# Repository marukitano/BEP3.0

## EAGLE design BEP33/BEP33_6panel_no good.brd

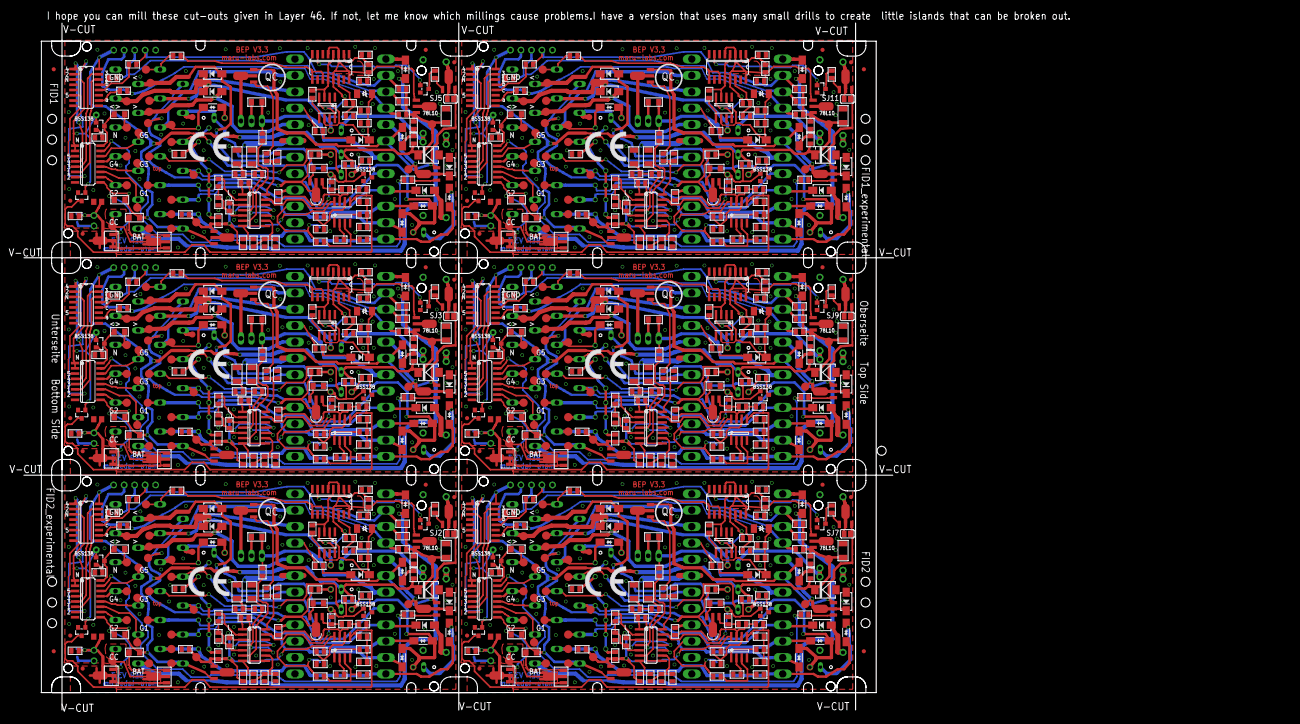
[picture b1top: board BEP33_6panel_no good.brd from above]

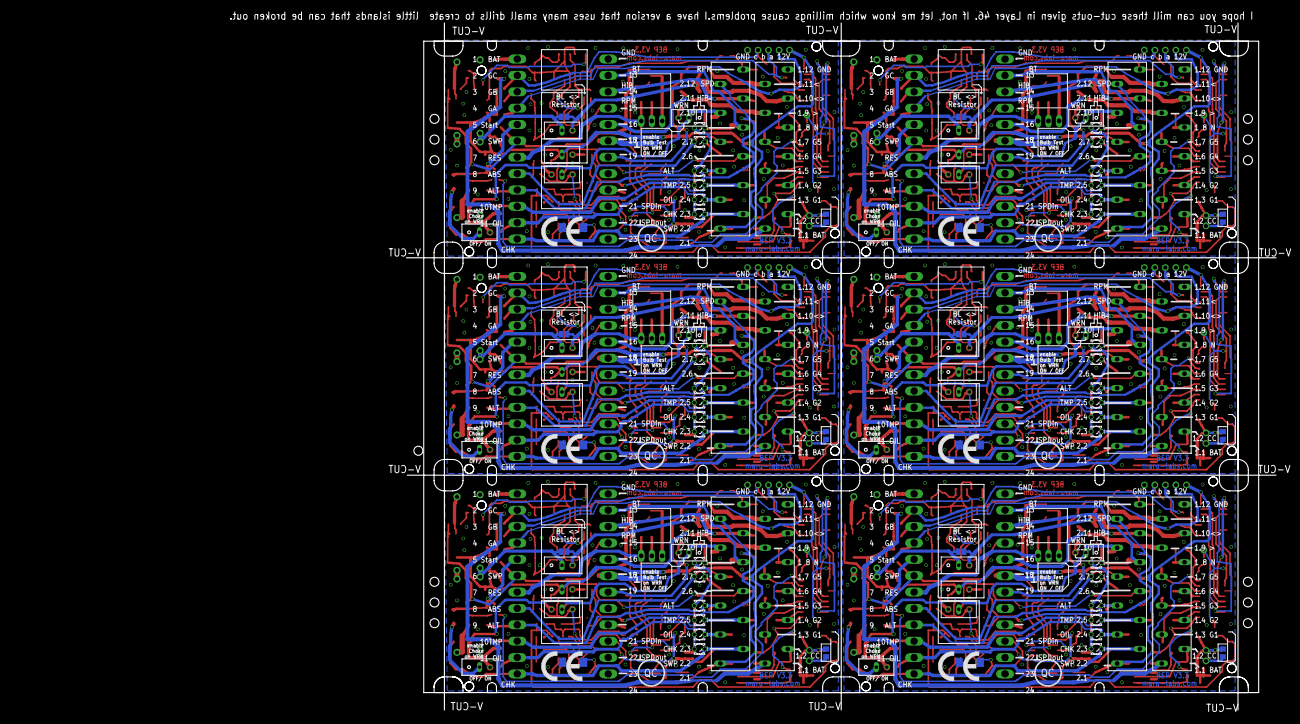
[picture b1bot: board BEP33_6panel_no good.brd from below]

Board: 2 copper layers, 210.4 x 166.2 mm, 904 parts (150 on the bottom side), 533 nets.

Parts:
1, 2, 3, 4, 5, 6, 7, 8, 9, 10, 11, 12: 12-PIN
6V, 6V1, 6V2, 6V3, 6V4, 6V5, 10V, 10V1, 10V2, 10V3, 10V4, 10V5: TPSB2.0; B2.0
C1, C3, C14, C16, C27, C28, C39, C40, C51, C52, C107, C108: 100u; C1206
C2, C13, C26, C38, C50, C62: 10u; C1206
C4, C11, C17, C24, C29, C36, C41, C48, C53, C60, C103, C104: 100nF,; C0805
C5, C12, C15, C18, C25, C30, C37, C42, C49, C54, C61, C101: 4.7u; C0805
C6, C7, C19, C20, C31, C32, C43, C44, C55, C56, C105, C106: 100nF.; C0805
C8, C21, C33, C45, C57, C109: 2.2nF; C0805
C9, C10, C22, C23, C34, C35, C46, C47, C58, C59, C102, C110: 100nF; C0805
D1, D2, D15, D16, D29, D30, D43, D44, D57, D58, D71, D72: SS12; DO-214AC_SLIM
D3, D5, D18, D19, D32, D33, D46, D47, D60, D61, D102, D103: 1N4007,; DO-214AC
D4, D17, D31, D45, D59, D73: Zen11; SOD-123_MINI-SMA
D6, D11, D20, D25, D34, D39, D48, D53, D62, D67, D105, D106: 1N4007.; DO-214AC
D7, D10, D21, D24, D35, D38, D49, D52, D63, D66, D107, D110: 1N5817; DO-214AC_SLIM
D8, D9, D22, D23, D36, D37, D50, D51, D64, D65, D108, D109: 1N5817.; DO-214AC_SLIM
D12, D26, D40, D54, D68, D112: 1N4007; DO-214AC
D13, D27, D41, D55, D69, D101: Zen15; DO214AA
D14, D28, D42, D56, D70, D104: SM6TDO214AA_BI; DO214AA_BI
FID1, FID2, FID3, FID4, FID5, FID6, FID7, FID8, FID9, FID10, FID11, FID12, FID13, FID14, FID15, FID16, FID17, FID18, FID19, FID20, FID21, FID22, FID101, FID102, FID103, FID104: FIDUCIAL; FIDUCIAL_1MM
FID1B, FID2B: FIDUCIALFIDUCIAL_1MM_WITH_SOLDERMASK; FIDUCIAL_1MM_WITH_SOLDERMASK
IC1, IC10, IC19, IC28, IC37, IC105: 4028; SO16
IC2, IC11, IC20, IC29, IC38, IC109: 317TO202H_NOHOLE; TO220H_NOHOLE
IC3, IC12, IC21, IC30, IC39, IC107: ULN2004; SO16
IC4, IC13, IC22, IC31, IC40, IC108: LM339; SO14
IC5, IC14, IC23, IC32, IC41, IC102: 78L06; SOT89_ROUND
IC6, IC15, IC24, IC33, IC42, IC110: 555; SO08
IC7, IC16, IC25, IC34, IC43, IC111: 4538; SO16
IC8, IC17, IC26, IC35, IC44, IC104: 78L10; SOT89_ROUND
IC9, IC18, IC27, IC36, IC45, IC101: LM2904; SO08
JP1, JP3, JP4, JP5, JP6, JP8, JP9, JP10, JP11, JP13, JP14, JP15, JP16, JP18, JP19, JP20, JP21, JP23, JP24, JP25, JP101, JP102, JP103, JP104: JP2_SMALLPADS
JP2, JP7, JP12, JP17, JP22, JP105: JP2E_ORIG; JP2_ORIG_SMALLPADS
LED1, LED2, LED3, LED4, LED5, LED6, LED7, LED8, LED9, LED10, LED11, LED12, LED13, LED14, LED15, LED16, LED17, LED18, LED19, LED20, LED21, LED22, LED23, LED24, LED25, LED26, LED27, LED28, LED29, LED30, LED101, LED102, LED103, LED104, LED105, LED106: LD260
Q1, Q3, Q9, Q10, Q11, Q13, Q19, Q20, Q21, Q23, Q29, Q30, Q31, Q33, Q39, Q40, Q41, Q43, Q49, Q50, Q51, Q53, Q106, Q107: J1; SOT-23
Q2, Q4, Q7, Q12, Q14, Q17, Q22, Q24, Q27, Q32, Q34, Q37, Q42, Q44, Q47, Q52, Q104, Q105: BA; SOT89
Q5, Q6, Q15, Q16, Q25, Q26, Q35, Q36, Q45, Q46, Q101, Q102: BA.; SOT89
Q8, Q18, Q28, Q38, Q48, Q103: MY; SOT89
R1, R2, R3, R10, R15, R16, R17, R22, R23, R41, R42, R56, R57, R58, R64, R70, R71, R72, R77, R78, R96, R97, R109, R110, R111, R125, R130, R135, R141, R155, R156, R157, R163, R169, R170, R171, R176, R177, R195, R196, R210, R211, R212, R218, R224, R225, R226, R231, R232, R250, R251, R265, R266, R267, R273, R279, R280, R281, R286, R287, R305, R306, R320, R321, R322, R328: 104; R0805
R4, R12, R13, R40, R61, R65, R66, R95, R138, R160, R164, R165, R194, R215, R219, R220, R249, R270, R274, R275, R304, R325, R329, R330: 100; R0805
R5, R9, R11, R36, R37, R59, R62, R68, R91, R92, R102, R106, R134, R158, R161, R167, R190, R191, R213, R216, R222, R245, R246, R268, R271, R277, R300, R301, R323, R326: 13; R1206
R6, R26, R48, R60, R81, R119, R133, R147, R159, R180, R202, R214, R235, R257, R269, R290, R312, R324: 2201; R0805
R7, R14, R45, R46, R67, R69, R100, R118, R127, R129, R136, R137, R166, R168, R199, R200, R221, R223, R254, R255, R276, R278, R309, R310: 47; V235/17_1MM
R8, R18, R28, R39, R63, R73, R83, R94, R105, R116, R126, R162, R172, R182, R193, R217, R227, R237, R248, R272, R282, R292, R303, R327: 4701; R0805
R19, R20, R25, R27, R49, R50, R53, R54, R74, R75, R80, R82, R107, R108, R113, R114, R120, R124, R132, R146, R148, R149, R152, R153, R173, R174, R179, R181, R203, R204, R207, R208, R228, R229, R234, R236, R258, R259, R262, R263, R283, R284, R289, R291, R313, R314, R317, R318: 1002; R0805
R21, R24, R76, R79, R121, R131, R175, R178, R230, R233, R285, R288: 1502; R0805
R29, R38, R44, R47, R52, R84, R93, R99, R117, R122, R123, R139, R140, R145, R151, R183, R192, R198, R201, R206, R238, R247, R253, R256, R261, R293, R302, R308, R311, R316: 2702; R0805
R30, R32, R35, R51, R85, R87, R90, R101, R112, R115, R128, R150, R184, R186, R189, R205, R239, R241, R244, R260, R294, R296, R299, R315: 102; R0805
R31, R55, R86, R103, R104, R154, R185, R209, R240, R264, R295, R319: R_user; R0805
R33, R88, R143, R187, R242, R297: (101); R0805
R34, R89, R142, R188, R243, R298: (1000); R0805
R43, R98, R144, R197, R252, R307: (1002); R0805
SJ1, SJ2, SJ3, SJ4, SJ5, SJ6, SJ7, SJ8, SJ9, SJ10, SJ11, SJ101: SJ
START, START1, START2, START3, START4, START5: TPSB2.0; B2.0
TP1, TP2, TP3, TP4, TP5, TP6, TP7, TP8, TP9, TP10, TP11, TP12, TP13, TP14, TP15, TP16, TP17, TP18, TP19, TP20, TP21, TP22, TP23, TP25, TP26, TP27, TP28, TP29, TP30, TP31, TP32, TP33, TP34, TP35, TP36, TP37, TP38, TP39, TP40, TP41, TP43, TP44, TP45, TP46, TP47, TP48, TP49, TP50, TP51, TP52, TP53, TP54, TP55, TP56, TP57, TP58, TP59, TP60, TP61, TP62, TP63, TP64, TP66, TP67, TP68, TP69, TP70, TP71, TP72, TP73, TP74, TP75, TP76, TP77, TP78, TP79, TP80, TP81, TP82, TP83, TP84, TP85, TP86, TP87, TP89, TP90, TP91, TP92, TP93, TP94, TP95, TP96, TP97, TP98, TP99, TP100, TP101, TP102, TP103, TP104, TP105, TP106, TP107, TP108, TP109, TP110, TP112, TP113, TP114, TP115, TP116, TP117, TP118, TP119, TP120, TP121, TP122, TP123, TP124, TP125, TP126, TP127, TP128, TP129, TP130, TP131, TP132, TP133, TP135, TP136, TP137, TP138: TPSB2.0; B2.0
TP24, TP42, TP65, TP88, TP111, TP134: TPSB1,27; B1,27
U$1, U$2, U$3, U$4, U$5, U$6, U$7, U$8, U$9, U$10, U$11, U$12: CE_10.00
X1, X4, X7, X10, X13, X101: 24-PIN_V2
X2, X5, X8, X11, X14, X103: 22-23-2051
X3, X6, X9, X12, X15, X102: 22-23-2021

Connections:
+10V: 10V.TP, 10V1.TP, 10V2.TP, 10V3.TP, 10V4.TP, 10V5.TP, C9.1, C22.1, C34.1, C46.1, C58.1, C102.1, IC6.4, IC6.8, IC7.3, IC7.5, IC7.13, IC7.16, IC8.1, IC15.4, IC15.8, IC16.3, IC16.5, IC16.13, IC16.16, IC17.1, IC24.4, IC24.8, IC25.3, IC25.5, IC25.13, IC25.16, IC26.1, IC33.4, IC33.8, IC34.3, IC34.5, IC34.13, IC34.16, IC35.1, IC42.4, IC42.8, IC43.3, IC43.5, IC43.13, IC43.16, IC44.1, IC104.1, IC110.4, IC110.8, IC111.3, IC111.5, IC111.13, IC111.16, R10.2, R47.2, R64.2, R139.2, R145.2, R163.2, R201.2, R218.2, R256.2, R273.2, R311.2, R328.2
+12V: 2.1, 4.1, 6.1, 8.1, 10.1, 12.1, C2.1, C13.1, C26.1, C38.1, C50.1, C62.1, D13.C, D27.C, D41.C, D55.C, D69.C, D101.C, IC1.16, IC3.9, IC5.3, IC8.3, IC10.16, IC12.9, IC14.3, IC17.3, IC19.16, IC21.9, IC23.3, IC26.3, IC28.16, IC30.9, IC32.3, IC35.3, IC37.16, IC39.9, IC41.3, IC44.3, IC102.3, IC104.3, IC105.16, IC107.9, JP1.2, JP6.2, JP11.2, JP16.2, JP21.2, JP101.2, R12.2, R13.2, R15.2, R16.2, R17.2, R36.1, R37.1, R41.1, R65.2, R66.2, R70.2, R71.2, R72.2, R91.1, R92.1, R96.1, R102.1, R106.1, R109.2, R110.2, R111.2, R135.1, R164.2, R165.2, R169.2, R170.2, R171.2, R190.1, R191.1, R195.1, R219.2, R220.2, R224.2, R225.2, R226.2, R245.1, R246.1, R250.1, R274.2, R275.2, R279.2, R280.2, R281.2, R300.1, R301.1, R305.1, R329.2, R330.2, TP12.TP, TP45.TP, TP68.TP, TP91.TP, TP114.TP, TP137.TP, X2.1, X5.1, X8.1, X11.1, X14.1, X103.1
+12V1: 2.11, Q103.2, R119.1, TP26.TP
+12V2: 4.11, Q8.2, R48.1, TP44.TP
+12V3: 6.11, Q18.2, R147.1, TP67.TP
+12V4: 8.11, Q28.2, R202.1, TP90.TP
+12V5: 10.11, Q38.2, R257.1, TP113.TP
+12V6: 12.11, Q48.2, R312.1, TP136.TP
GND: 1.12, 3.12, 5.12, 7.12, 9.12, 11.12, C1.2, C2.2, C3.2, C4.2, C5.2, C6.2, C7.1, C8.1, C9.2, C10.2, C11.2, C12.1, C13.2, C14.2, C15.1, C16.2, C17.2, C18.2, C19.2, C20.1, C21.1, C22.2, C23.2, C24.2, C25.1, C26.2, C27.2, C28.2, C29.2, C30.2, C31.2, C32.1, C33.1, C34.2, C35.2, C36.2, C37.1, C38.2, C39.2, C40.2, C41.2, C42.2, C43.2, C44.1, C45.1, C46.2, C47.2, C48.2, C49.1, C50.2, C51.2, C52.2, C53.2, C54.2, C55.2, C56.1, C57.1, C58.2, C59.2, C60.2, C61.1, C62.2, C101.2, C102.2, C103.2, C104.2, C105.2, C106.1, C107.2, C108.2, C109.1, C110.2, D4.A, D11.1, D13.A, D14.A, D17.A, D25.1, D27.A, D28.A, D31.A, D39.1, D41.A, D42.A, D45.A, D53.1, D55.A, D56.A, D59.A, D67.1, D69.A, D70.A, D73.A, D101.A, D104.A, D105.1, IC1.8, IC1.11, IC3.8, IC4.12, IC5.2, IC5.2@1, IC6.1, IC7.1, IC7.8, IC7.15, IC8.2, IC8.2@1, IC9.4, IC10.8, IC10.11, IC12.8, IC13.12, IC14.2, IC14.2@1, IC15.1, IC16.1, IC16.8, IC16.15, IC17.2, IC17.2@1, IC18.4, IC19.8, IC19.11, IC21.8, IC22.12, IC23.2, IC23.2@1, IC24.1, IC25.1, IC25.8, IC25.15, IC26.2, IC26.2@1, IC27.4, IC28.8, IC28.11, IC30.8, IC31.12, IC32.2, IC32.2@1, IC33.1, IC34.1, IC34.8, IC34.15, IC35.2, IC35.2@1, IC36.4, IC37.8, IC37.11, IC39.8, IC40.12, IC41.2, IC41.2@1, IC42.1, IC43.1, IC43.8, IC43.15, IC44.2, IC44.2@1, IC45.4, IC101.4, IC102.2, IC102.2@1, IC104.2, IC104.2@1, IC105.8, IC105.11, IC107.8, IC108.12, IC110.1, IC111.1, IC111.8, IC111.15, Q1.2, Q3.2, Q9.2, Q11.2, Q13.2, Q19.2, Q21.2, Q23.2, Q29.2, Q31.2, Q33.2, Q39.2, Q41.2, Q43.2, Q49.2, Q51.2, Q53.2, Q107.2, R4.1, R5.2, R6.2, R19.1, R25.1, R29.1, R30.2, R31.2, R33.2, R42.2, R45.1, R46.1, R54.1, R55.2, R59.2, R60.2, R61.1, R74.1, R80.1, R84.1, R85.2, R86.2, R88.2, R97.2, R100.1, R101.2, R103.2, R104.2, R107.1, R114.1, R118.1, R123.1, R132.1, R136.1, R137.1, R141.2, R143.2, R153.1, R154.2, R158.2, R159.2, R160.1, R173.1, R179.1, R183.1, R184.2, R185.2, R187.2, R196.2, R199.1, R200.1, R208.1, R209.2, R213.2, R214.2, R215.1, R228.1, R234.1, R238.1, R239.2, R240.2, R242.2, R251.2, R254.1, R255.1, R263.1, R264.2, R268.2, R269.2, R270.1, R283.1, R289.1, R293.1, R294.2, R295.2, R297.2, R306.2, R309.1, R310.1, R318.1, R319.2, R323.2, R324.2, R325.1, X1.13, X1.18, X1.23, X2.5, X3.1, X4.13, X4.18, X4.23, X5.5, X6.1, X7.13, X7.18, X7.23, X8.5, X9.1, X10.13, X10.18, X10.23, X11.5, X12.1, X13.13, X13.18, X13.23, X14.5, X15.1, X101.13, X101.18, X101.23, X102.1, X103.5
unnamed: 2.9, D107.1, D108.1, JP102.1, JP103.2, TP24.TP
unnamed: IC105.10, R3.1, R3.2, R111.1, X101.4, X103.2
unnamed: IC105.13, R2.1, R2.2, R110.1, X101.3, X103.3
unnamed: 2.7, LED101.A, TP22.TP, X101.8
unnamed: Q101.3, R102.2
unnamed: Q2.1, R8.1
unnamed: IC101.2, R107.2
unnamed: R127.2, R129.1
unnamed: Q102.3, R106.2
unnamed: D105.2, Q104.2, START.TP, X101.5
unnamed: 2.2, D109.2, LED102.K, TP16.TP, X101.12
unnamed: 2.3, D108.2, LED103.K, TP17.TP, X101.11
unnamed: 2.4, D107.2, LED104.K, TP18.TP, X101.10
unnamed: IC109.3, Q105.2
unnamed: IC108.6, IC108.8, R120.1
unnamed: IC105.12, R1.1, R1.2, R109.1, X101.2, X103.4
unnamed: IC105.15, IC107.5
unnamed: 2.8, D110.2, LED106.K, TP23.TP, X101.14
unnamed: 1.9, D102.1, TP9.TP, X101.17
unnamed: 1.11, D103.1, TP11.TP, X101.19
unnamed: IC111.9, IC111.11, R146.2
unnamed: D104.C, R105.2, X101.22
unnamed: C101.1, IC101.3, R105.1
unnamed: 1.6, IC107.13, TP6.TP
unnamed: 1.7, IC107.14, TP7.TP
unnamed: D1.2, R12.1, R13.1
unnamed: 2.6, JP105.2, TP21.TP
unnamed: JP101.1, R119.2
unnamed: C105.1, IC108.9, R122.2, R123.2
unnamed: C106.2, IC108.14, R126.2
unnamed: Q3.3, R8.2
unnamed: LED101.K, R143.1
unnamed: IC109.1, R120.2, R134.1, X101.7
unnamed: Q105.1, R126.1
unnamed: IC105.2, IC107.7
unnamed: 1.3, IC107.11, TP3.TP
unnamed: 1.5, IC107.12, TP5.TP
unnamed: LED102.A, LED103.A, LED104.A, LED105.A, LED106.A, R142.1
unnamed: R140.2, X101.16
unnamed: Q104.1, R128.2
unnamed: IC105.3, IC107.1, IC107.2, Q1.1, Q106.1
unnamed: C107.1, R125.1, R130.2
unnamed: C108.1, IC108.4, IC108.10, R130.1
unnamed: IC108.5, IC108.11, R131.1, R132.2, R133.2
unnamed: Q107.3, R138.2
unnamed: IC111.7, Q3.1
unnamed: IC105.1, IC107.4
unnamed: R115.1, X101.21
unnamed: IC107.16, Q106.3, R9.1
unnamed: 2.10, TP25.TP, X101.15
unnamed: D106.1, R127.1
unnamed: 2.5, D106.2, LED105.K, TP19.TP, X101.9
unnamed: IC105.14, IC107.6
unnamed: Q101.1, Q102.1, Q102.2, R101.1, R103.1, R104.1, X102.2
unnamed: 1.8, R9.2, TP8.TP
unnamed: 1.2, Q101.2, TP2.TP
unnamed: IC108.13, JP105.1, Q107.1, R135.2
unnamed: IC105.6, IC107.3
unnamed: IC109.2, R134.2
unnamed: IC110.5, R144.2
unnamed: 1.4, IC107.10, TP4.TP
unnamed: 1.1, D2.2, TP1.TP
unnamed: IC108.7, R121.1, R122.1
unnamed: Q106.2, R4.2
unnamed: Q103.1, R6.1, R116.2
unnamed: IC110.3, IC111.4, IC111.12, R144.1
unnamed: D112.1, R140.1
unnamed: IC107.15, R128.1
unnamed: C110.1, IC111.14, R145.1
unnamed: 2.12, R146.1, TP13.TP
unnamed: D2.1, X101.1
unnamed: IC101.1, R108.2
unnamed: 1.10, D102.2, D103.2, JP104.1, SJ101.1, TP10.TP
unnamed: JP104.2, R136.2, R137.2, SJ101.2
unnamed: D109.1, JP102.2
unnamed: C103.1, R108.1, R112.1
unnamed: IC101.5, Q1.3, R112.2, R117.2
unnamed: D110.1, JP103.1
unnamed: JP105.3, R138.1
unnamed: Q103.3, R5.1
unnamed: IC101.6, R113.1, R114.2
unnamed: C109.2, D4.C, D112.2, IC110.2, IC110.6, R141.1
unnamed: C15.2, IC111.2, R10.1
unnamed: Q2.2, R129.2, SJ2.2
unnamed: IC101.7, R115.2, R116.1, R117.1
unnamed: IC108.2, R133.1
unnamed: R7.2, R14.1
unnamed: 4.9, D7.1, D8.1, JP3.1, JP4.2, TP42.TP
unnamed: IC1.10, R17.1, R58.1, R58.2, X1.4, X2.2
unnamed: IC1.13, R16.1, R57.1, R57.2, X1.3, X2.3
unnamed: D11.2, Q4.2, START1.TP, X1.5
unnamed: IC1.12, R15.1, R56.1, R56.2, X1.2, X2.4
unnamed: 4.7, LED5.A, TP40.TP, X1.8
unnamed: 4.2, D9.2, LED1.K, TP35.TP, X1.12
unnamed: 4.3, D8.2, LED2.K, TP36.TP, X1.11
unnamed: 4.4, D7.2, LED3.K, TP37.TP, X1.10
unnamed: 4.8, D10.2, LED6.K, TP41.TP, X1.14
unnamed: 3.9, D3.1, TP32.TP, X1.17
unnamed: 3.11, D5.1, TP34.TP, X1.19
unnamed: D14.C, R18.2, X1.22
unnamed: C5.1, IC9.3, R18.1
unnamed: IC4.1, R22.2, R27.2
unnamed: C1.1, R22.1, R23.2
unnamed: C3.1, IC4.4, IC4.10, R23.1
unnamed: IC4.5, IC4.11, R24.1, R25.2, R26.2
unnamed: C6.1, IC4.9, R29.2, R38.2
unnamed: C7.2, IC4.14, R28.2
unnamed: Q7.1, R28.1
unnamed: IC1.2, IC3.7
unnamed: 3.5, IC3.12, TP28.TP
unnamed: IC1.1, IC3.4
unnamed: 4.10, TP43.TP, X1.15
unnamed: 4.5, D6.2, LED4.K, TP38.TP, X1.9
unnamed: D6.1, R7.1
unnamed: IC1.6, IC3.3
unnamed: 3.4, IC3.10, TP27.TP
unnamed: IC2.1, R11.1, R20.2, X1.7
unnamed: IC4.6, IC4.8, R20.1
unnamed: 3.2, Q6.2, TP15.TP
unnamed: 3.1, D16.2, TP14.TP
unnamed: R44.2, X1.16
unnamed: IC1.15, IC3.5
unnamed: 3.6, IC3.13, TP29.TP
unnamed: 3.7, IC3.14, TP30.TP
unnamed: 4.6, JP2.2, TP39.TP
unnamed: LED5.K, R33.1
unnamed: LED1.A, LED2.A, LED3.A, LED4.A, LED6.A, R34.1
unnamed: Q4.1, R35.2
unnamed: IC1.3, IC3.1, IC3.2, Q10.1, Q11.1
unnamed: IC1.14, IC3.6
unnamed: 3.3, IC3.11, TP20.TP
unnamed: Q5.1, Q5.2, Q6.1, R30.1, R31.1, R55.1, X3.2
unnamed: Q6.3, R37.2
unnamed: Q5.3, R36.2
unnamed: IC4.7, R21.1, R38.1
unnamed: IC9.2, R19.2
unnamed: Q8.1, R39.2, R60.1
unnamed: Q9.3, R40.2
unnamed: IC2.2, R11.2
unnamed: IC2.3, Q7.2
unnamed: IC6.5, R43.2
unnamed: IC6.3, IC7.4, IC7.12, R43.1
unnamed: D12.1, R44.1
unnamed: 3.10, D3.2, D5.2, JP5.1, SJ1.1, TP33.TP
unnamed: JP5.2, R45.2, R46.2, SJ1.2
unnamed: IC7.9, IC7.11, R49.2
unnamed: C10.1, IC7.14, R47.1
unnamed: JP1.1, R48.2
unnamed: IC3.15, R35.1
unnamed: 4.12, R49.1, TP46.TP
unnamed: D9.1, JP3.2
unnamed: IC9.1, R50.2
unnamed: C11.1, R50.1, R51.1
unnamed: IC9.5, Q11.3, R51.2, R52.2
unnamed: IC9.6, R53.1, R54.2
unnamed: D10.1, JP4.1
unnamed: JP2.3, R40.1
unnamed: IC4.13, JP2.1, Q9.1, R41.2
unnamed: R32.1, X1.21
unnamed: IC3.16, Q10.3, R62.1
unnamed: D15.2, R65.1, R66.1
unnamed: 3.8, R62.2, TP31.TP
unnamed: Q10.2, R61.2
unnamed: D16.1, X1.1
unnamed: Q8.3, R59.1
unnamed: C8.2, D12.2, D17.C, IC6.2, IC6.6, R42.1
unnamed: Q12.1, R63.1
unnamed: Q13.3, R63.2
unnamed: Q12.2, R14.2, SJ3.2
unnamed: IC9.7, R32.2, R39.1, R52.1
unnamed: IC4.2, R26.1
unnamed: IC7.7, Q13.1
unnamed: C12.2, IC7.2, R64.1
unnamed: R67.2, R69.1
unnamed: 6.9, D21.1, D22.1, JP8.1, JP9.2, TP65.TP
unnamed: IC10.10, R72.1, R157.1, R157.2, X4.4, X5.2
unnamed: IC10.13, R71.1, R156.1, R156.2, X4.3, X5.3
unnamed: D25.2, Q14.2, START2.TP, X4.5
unnamed: IC10.12, R70.1, R155.1, R155.2, X4.2, X5.4
unnamed: 6.7, LED11.A, TP63.TP, X4.8
unnamed: 6.2, D23.2, LED7.K, TP58.TP, X4.12
unnamed: 6.3, D22.2, LED8.K, TP59.TP, X4.11
unnamed: 6.4, D21.2, LED9.K, TP60.TP, X4.10
unnamed: 6.8, D24.2, LED12.K, TP64.TP, X4.14
unnamed: 5.9, D18.1, TP55.TP, X4.17
unnamed: 5.11, D19.1, TP57.TP, X4.19
unnamed: D28.C, R73.2, X4.22
unnamed: C18.1, IC18.3, R73.1
unnamed: IC13.1, R77.2, R82.2
unnamed: C14.1, R77.1, R78.2
unnamed: C16.1, IC13.4, IC13.10, R78.1
unnamed: IC13.5, IC13.11, R79.1, R80.2, R81.2
unnamed: C19.1, IC13.9, R84.2, R93.2
unnamed: C20.2, IC13.14, R83.2
unnamed: Q17.1, R83.1
unnamed: IC10.2, IC12.7
unnamed: 5.5, IC12.12, TP51.TP
unnamed: IC10.1, IC12.4
unnamed: 6.10, TP66.TP, X4.15
unnamed: 6.5, D20.2, LED10.K, TP61.TP, X4.9
unnamed: D20.1, R67.1
unnamed: IC10.6, IC12.3
unnamed: 5.4, IC12.10, TP50.TP
unnamed: IC11.1, R68.1, R75.2, X4.7
unnamed: IC13.6, IC13.8, R75.1
unnamed: 5.2, Q16.2, TP48.TP
unnamed: 5.1, D30.2, TP47.TP
unnamed: R99.2, X4.16
unnamed: IC10.15, IC12.5
unnamed: 5.6, IC12.13, TP52.TP
unnamed: 5.7, IC12.14, TP53.TP
unnamed: 6.6, JP7.2, TP62.TP
unnamed: LED11.K, R88.1
unnamed: LED7.A, LED8.A, LED9.A, LED10.A, LED12.A, R89.1
unnamed: Q14.1, R90.2
unnamed: IC10.3, IC12.1, IC12.2, Q20.1, Q21.1
unnamed: IC10.14, IC12.6
unnamed: 5.3, IC12.11, TP49.TP
unnamed: Q15.1, Q15.2, Q16.1, R85.1, R86.1, R154.1, X6.2
unnamed: Q16.3, R92.2
unnamed: Q15.3, R91.2
unnamed: IC13.7, R76.1, R93.1
unnamed: IC18.2, R74.2
unnamed: Q18.1, R94.2, R159.1
unnamed: Q19.3, R95.2
unnamed: IC11.2, R68.2
unnamed: IC11.3, Q17.2
unnamed: IC15.5, R98.2
unnamed: IC15.3, IC16.4, IC16.12, R98.1
unnamed: D26.1, R99.1
unnamed: 5.10, D18.2, D19.2, JP10.1, SJ4.1, TP56.TP
unnamed: JP10.2, R100.2, R118.2, SJ4.2
unnamed: IC16.9, IC16.11, R148.2
unnamed: C23.1, IC16.14, R139.1
unnamed: JP6.1, R147.2
unnamed: IC12.15, R90.1
unnamed: 6.12, R148.1, TP69.TP
unnamed: D23.1, JP8.2
unnamed: IC18.1, R149.2
unnamed: C24.1, R149.1, R150.1
unnamed: IC18.5, Q21.3, R150.2, R151.2
unnamed: IC18.6, R152.1, R153.2
unnamed: D24.1, JP9.1
unnamed: JP7.3, R95.1
unnamed: IC13.13, JP7.1, Q19.1, R96.2
unnamed: R87.1, X4.21
unnamed: IC12.16, Q20.3, R161.1
unnamed: D29.2, R164.1, R165.1
unnamed: 5.8, R161.2, TP54.TP
unnamed: Q20.2, R160.2
unnamed: D30.1, X4.1
unnamed: Q18.3, R158.1
unnamed: C21.2, D26.2, D31.C, IC15.2, IC15.6, R97.1
unnamed: Q22.1, R162.1
unnamed: Q23.3, R162.2
unnamed: Q22.2, R69.2, SJ5.2
unnamed: IC18.7, R87.2, R94.1, R151.1
unnamed: IC13.2, R81.1
unnamed: IC16.7, Q23.1
unnamed: C25.2, IC16.2, R163.1
unnamed: IC108.1, R124.2, R125.2
unnamed: R166.2, R168.1
unnamed: 8.9, D35.1, D36.1, JP13.1, JP14.2, TP88.TP
unnamed: IC19.10, R171.1, R212.1, R212.2, X7.4, X8.2
unnamed: IC19.13, R170.1, R211.1, R211.2, X7.3, X8.3
unnamed: D39.2, Q24.2, START3.TP, X7.5
unnamed: IC19.12, R169.1, R210.1, R210.2, X7.2, X8.4
unnamed: 8.7, LED17.A, TP86.TP, X7.8
unnamed: 8.2, D37.2, LED13.K, TP81.TP, X7.12
unnamed: 8.3, D36.2, LED14.K, TP82.TP, X7.11
unnamed: 8.4, D35.2, LED15.K, TP83.TP, X7.10
unnamed: 8.8, D38.2, LED18.K, TP87.TP, X7.14
unnamed: 7.9, D32.1, TP78.TP, X7.17
unnamed: 7.11, D33.1, TP80.TP, X7.19
unnamed: D42.C, R172.2, X7.22
unnamed: C30.1, IC27.3, R172.1
unnamed: IC22.1, R176.2, R181.2
unnamed: C27.1, R176.1, R177.2
unnamed: C28.1, IC22.4, IC22.10, R177.1
unnamed: IC22.5, IC22.11, R178.1, R179.2, R180.2
unnamed: C31.1, IC22.9, R183.2, R192.2
unnamed: C32.2, IC22.14, R182.2
unnamed: Q27.1, R182.1
unnamed: IC19.2, IC21.7
unnamed: 7.5, IC21.12, TP74.TP
unnamed: IC19.1, IC21.4
unnamed: 8.10, TP89.TP, X7.15
unnamed: 8.5, D34.2, LED16.K, TP84.TP, X7.9
unnamed: D34.1, R166.1
unnamed: IC19.6, IC21.3
unnamed: 7.4, IC21.10, TP73.TP
unnamed: IC20.1, R167.1, R174.2, X7.7
unnamed: IC22.6, IC22.8, R174.1
unnamed: 7.2, Q26.2, TP71.TP
unnamed: 7.1, D44.2, TP70.TP
unnamed: R198.2, X7.16
unnamed: IC19.15, IC21.5
unnamed: 7.6, IC21.13, TP75.TP
unnamed: 7.7, IC21.14, TP76.TP
unnamed: 8.6, JP12.2, TP85.TP
unnamed: LED17.K, R187.1
unnamed: LED13.A, LED14.A, LED15.A, LED16.A, LED18.A, R188.1
unnamed: Q24.1, R189.2
unnamed: IC19.3, IC21.1, IC21.2, Q30.1, Q31.1
unnamed: IC19.14, IC21.6
unnamed: 7.3, IC21.11, TP72.TP
unnamed: Q25.1, Q25.2, Q26.1, R184.1, R185.1, R209.1, X9.2
unnamed: Q26.3, R191.2
unnamed: Q25.3, R190.2
unnamed: IC22.7, R175.1, R192.1
unnamed: IC27.2, R173.2
unnamed: Q28.1, R193.2, R214.1
unnamed: Q29.3, R194.2
unnamed: IC20.2, R167.2
unnamed: IC20.3, Q27.2
unnamed: IC24.5, R197.2
unnamed: IC24.3, IC25.4, IC25.12, R197.1
unnamed: D40.1, R198.1
unnamed: 7.10, D32.2, D33.2, JP15.1, SJ6.1, TP79.TP
unnamed: JP15.2, R199.2, R200.2, SJ6.2
unnamed: IC25.9, IC25.11, R203.2
unnamed: C35.1, IC25.14, R201.1
unnamed: JP11.1, R202.2
unnamed: IC21.15, R189.1
unnamed: 8.12, R203.1, TP92.TP
unnamed: D37.1, JP13.2
unnamed: IC27.1, R204.2
unnamed: C36.1, R204.1, R205.1
unnamed: IC27.5, Q31.3, R205.2, R206.2
unnamed: IC27.6, R207.1, R208.2
unnamed: D38.1, JP14.1
unnamed: JP12.3, R194.1
unnamed: IC22.13, JP12.1, Q29.1, R195.2
unnamed: R186.1, X7.21
unnamed: IC21.16, Q30.3, R216.1
unnamed: D43.2, R219.1, R220.1
unnamed: 7.8, R216.2, TP77.TP
unnamed: Q30.2, R215.2
unnamed: D44.1, X7.1
unnamed: Q28.3, R213.1
unnamed: C33.2, D40.2, D45.C, IC24.2, IC24.6, R196.1
unnamed: Q32.1, R217.1
unnamed: Q33.3, R217.2
unnamed: Q32.2, R168.2, SJ7.2
unnamed: IC27.7, R186.2, R193.1, R206.1
unnamed: IC22.2, R180.1
unnamed: IC25.7, Q33.1
unnamed: C37.2, IC25.2, R218.1
unnamed: R221.2, R223.1
unnamed: 10.9, D49.1, D50.1, JP18.1, JP19.2, TP111.TP
unnamed: IC28.10, R226.1, R267.1, R267.2, X10.4, X11.2
unnamed: IC28.13, R225.1, R266.1, R266.2, X10.3, X11.3
unnamed: D53.2, Q34.2, START4.TP, X10.5
unnamed: IC28.12, R224.1, R265.1, R265.2, X10.2, X11.4
unnamed: 10.7, LED23.A, TP109.TP, X10.8
unnamed: 10.2, D51.2, LED19.K, TP104.TP, X10.12
unnamed: 10.3, D50.2, LED20.K, TP105.TP, X10.11
unnamed: 10.4, D49.2, LED21.K, TP106.TP, X10.10
unnamed: 10.8, D52.2, LED24.K, TP110.TP, X10.14
unnamed: 9.9, D46.1, TP101.TP, X10.17
unnamed: 9.11, D47.1, TP103.TP, X10.19
unnamed: D56.C, R227.2, X10.22
unnamed: C42.1, IC36.3, R227.1
unnamed: IC31.1, R231.2, R236.2
unnamed: C39.1, R231.1, R232.2
unnamed: C40.1, IC31.4, IC31.10, R232.1
unnamed: IC31.5, IC31.11, R233.1, R234.2, R235.2
unnamed: C43.1, IC31.9, R238.2, R247.2
unnamed: C44.2, IC31.14, R237.2
unnamed: Q37.1, R237.1
unnamed: IC28.2, IC30.7
unnamed: 9.5, IC30.12, TP97.TP
unnamed: IC28.1, IC30.4
unnamed: 10.10, TP112.TP, X10.15
unnamed: 10.5, D48.2, LED22.K, TP107.TP, X10.9
unnamed: D48.1, R221.1
unnamed: IC28.6, IC30.3
unnamed: 9.4, IC30.10, TP96.TP
unnamed: IC29.1, R222.1, R229.2, X10.7
unnamed: IC31.6, IC31.8, R229.1
unnamed: 9.2, Q36.2, TP94.TP
unnamed: 9.1, D58.2, TP93.TP
unnamed: R253.2, X10.16
unnamed: IC28.15, IC30.5
unnamed: 9.6, IC30.13, TP98.TP
unnamed: 9.7, IC30.14, TP99.TP
unnamed: 10.6, JP17.2, TP108.TP
unnamed: LED23.K, R242.1
unnamed: LED19.A, LED20.A, LED21.A, LED22.A, LED24.A, R243.1
unnamed: Q34.1, R244.2
unnamed: IC28.3, IC30.1, IC30.2, Q40.1, Q41.1
unnamed: IC28.14, IC30.6
unnamed: 9.3, IC30.11, TP95.TP
unnamed: Q35.1, Q35.2, Q36.1, R239.1, R240.1, R264.1, X12.2
unnamed: Q36.3, R246.2
unnamed: Q35.3, R245.2
unnamed: IC31.7, R230.1, R247.1
unnamed: IC36.2, R228.2
unnamed: Q38.1, R248.2, R269.1
unnamed: Q39.3, R249.2
unnamed: IC29.2, R222.2
unnamed: IC29.3, Q37.2
unnamed: IC33.5, R252.2
unnamed: IC33.3, IC34.4, IC34.12, R252.1
unnamed: D54.1, R253.1
unnamed: 9.10, D46.2, D47.2, JP20.1, SJ8.1, TP102.TP
unnamed: JP20.2, R254.2, R255.2, SJ8.2
unnamed: IC34.9, IC34.11, R258.2
unnamed: C47.1, IC34.14, R256.1
unnamed: JP16.1, R257.2
unnamed: IC30.15, R244.1
unnamed: 10.12, R258.1, TP115.TP
unnamed: D51.1, JP18.2
unnamed: IC36.1, R259.2
unnamed: C48.1, R259.1, R260.1
unnamed: IC36.5, Q41.3, R260.2, R261.2
unnamed: IC36.6, R262.1, R263.2
unnamed: D52.1, JP19.1
unnamed: JP17.3, R249.1
unnamed: IC31.13, JP17.1, Q39.1, R250.2
unnamed: R241.1, X10.21
unnamed: IC30.16, Q40.3, R271.1
unnamed: D57.2, R274.1, R275.1
unnamed: 9.8, R271.2, TP100.TP
unnamed: Q40.2, R270.2
unnamed: D58.1, X10.1
unnamed: Q38.3, R268.1
unnamed: C45.2, D54.2, D59.C, IC33.2, IC33.6, R251.1
unnamed: Q42.1, R272.1
unnamed: Q43.3, R272.2
unnamed: Q42.2, R223.2, SJ9.2
unnamed: IC36.7, R241.2, R248.1, R261.1
unnamed: IC31.2, R235.1
unnamed: IC34.7, Q43.1
unnamed: C49.2, IC34.2, R273.1
unnamed: R276.2, R278.1
unnamed: 12.9, D63.1, D64.1, JP23.1, JP24.2, TP134.TP
unnamed: IC37.10, R281.1, R322.1, R322.2, X13.4, X14.2
unnamed: IC37.13, R280.1, R321.1, R321.2, X13.3, X14.3
unnamed: D67.2, Q44.2, START5.TP, X13.5
unnamed: IC37.12, R279.1, R320.1, R320.2, X13.2, X14.4
unnamed: 12.7, LED29.A, TP132.TP, X13.8
unnamed: 12.2, D65.2, LED25.K, TP127.TP, X13.12
unnamed: 12.3, D64.2, LED26.K, TP128.TP, X13.11
unnamed: 12.4, D63.2, LED27.K, TP129.TP, X13.10
unnamed: 12.8, D66.2, LED30.K, TP133.TP, X13.14
unnamed: 11.9, D60.1, TP124.TP, X13.17
unnamed: 11.11, D61.1, TP126.TP, X13.19
unnamed: D70.C, R282.2, X13.22
unnamed: C54.1, IC45.3, R282.1
unnamed: IC40.1, R286.2, R291.2
unnamed: C51.1, R286.1, R287.2
unnamed: C52.1, IC40.4, IC40.10, R287.1
unnamed: IC40.5, IC40.11, R288.1, R289.2, R290.2
unnamed: C55.1, IC40.9, R293.2, R302.2
unnamed: C56.2, IC40.14, R292.2
unnamed: Q47.1, R292.1
unnamed: IC37.2, IC39.7
unnamed: 11.5, IC39.12, TP120.TP
unnamed: IC37.1, IC39.4
unnamed: 12.10, TP135.TP, X13.15
unnamed: 12.5, D62.2, LED28.K, TP130.TP, X13.9
unnamed: D62.1, R276.1
unnamed: IC37.6, IC39.3
unnamed: 11.4, IC39.10, TP119.TP
unnamed: IC38.1, R277.1, R284.2, X13.7
unnamed: IC40.6, IC40.8, R284.1
unnamed: 11.2, Q46.2, TP117.TP
unnamed: 11.1, D72.2, TP116.TP
unnamed: R308.2, X13.16
unnamed: IC37.15, IC39.5
unnamed: 11.6, IC39.13, TP121.TP
unnamed: 11.7, IC39.14, TP122.TP
unnamed: 12.6, JP22.2, TP131.TP
unnamed: LED29.K, R297.1
unnamed: LED25.A, LED26.A, LED27.A, LED28.A, LED30.A, R298.1
unnamed: Q44.1, R299.2
unnamed: IC37.3, IC39.1, IC39.2, Q50.1, Q51.1
unnamed: IC37.14, IC39.6
unnamed: 11.3, IC39.11, TP118.TP
unnamed: Q45.1, Q45.2, Q46.1, R294.1, R295.1, R319.1, X15.2
unnamed: Q46.3, R301.2
unnamed: Q45.3, R300.2
unnamed: IC40.7, R285.1, R302.1
unnamed: IC45.2, R283.2
unnamed: Q48.1, R303.2, R324.1
unnamed: Q49.3, R304.2
unnamed: IC38.2, R277.2
unnamed: IC38.3, Q47.2
unnamed: IC42.5, R307.2
unnamed: IC42.3, IC43.4, IC43.12, R307.1
unnamed: D68.1, R308.1
unnamed: 11.10, D60.2, D61.2, JP25.1, SJ10.1, TP125.TP
unnamed: JP25.2, R309.2, R310.2, SJ10.2
unnamed: IC43.9, IC43.11, R313.2
unnamed: C59.1, IC43.14, R311.1
unnamed: JP21.1, R312.2
unnamed: IC39.15, R299.1
unnamed: 12.12, R313.1, TP138.TP
unnamed: D65.1, JP23.2
unnamed: IC45.1, R314.2
unnamed: C60.1, R314.1, R315.1
unnamed: IC45.5, Q51.3, R315.2, R316.2
unnamed: IC45.6, R317.1, R318.2
unnamed: D66.1, JP24.1
unnamed: JP22.3, R304.1
unnamed: IC40.13, JP22.1, Q49.1, R305.2
unnamed: R296.1, X13.21
unnamed: IC39.16, Q50.3, R326.1
unnamed: D71.2, R329.1, R330.1
unnamed: 11.8, R326.2, TP123.TP
unnamed: Q50.2, R325.2
unnamed: D72.1, X13.1
unnamed: Q48.3, R323.1
unnamed: C57.2, D68.2, D73.C, IC42.2, IC42.6, R306.1
unnamed: Q52.1, R327.1
unnamed: Q53.3, R327.2
unnamed: Q52.2, R278.2, SJ11.2
unnamed: IC45.7, R296.2, R303.1, R316.1
unnamed: IC40.2, R290.1
unnamed: IC43.7, Q53.1
unnamed: C61.2, IC43.2, R328.1
V+: D1.1, D15.1, D29.1, D43.1, D57.1, D71.1, Q2.3, Q4.3, Q7.3, Q12.3, Q14.3, Q17.3, Q22.3, Q24.3, Q27.3, Q32.3, Q34.3, Q37.3, Q42.3, Q44.3, Q47.3, Q52.3, Q104.3, Q105.3, SJ2.1, SJ3.1, SJ5.1, SJ7.1, SJ9.1, SJ11.1, X1.6, X4.6, X7.6, X10.6, X13.6, X101.6
VCC: 6V.TP, 6V1.TP, 6V2.TP, 6V3.TP, 6V4.TP, 6V5.TP, C4.1, C17.1, C29.1, C41.1, C53.1, C104.1, IC4.3, IC5.1, IC9.8, IC13.3, IC14.1, IC18.8, IC22.3, IC23.1, IC27.8, IC31.3, IC32.1, IC36.8, IC40.3, IC41.1, IC45.8, IC101.8, IC102.1, IC108.3, R21.2, R24.2, R27.1, R34.2, R53.2, R76.2, R79.2, R82.1, R89.2, R113.2, R121.2, R124.1, R131.2, R142.2, R152.2, R175.2, R178.2, R181.1, R188.2, R207.2, R230.2, R233.2, R236.1, R243.2, R262.2, R285.2, R288.2, R291.1, R298.2, R317.2

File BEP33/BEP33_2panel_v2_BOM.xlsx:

Qty | Value | Device | Package | Parts | Description | MF | MPN | OC_FARNELL | OC_NEWARK | TP | TP_SIGNAL_NAME | VALUE
2 | 100nF | CERAMIC-100NF-50V-10%-X7R(0805) | C0805 | C102, C110 | 302010165 |  | CC0805KRX7R9BB104 |  |  |  |  | 10K
2 | 100nF, | CERAMIC-100NF-50V-10%-X7R(0805) | C0805 | C103, C104 | 302010165 |  | CC0805KRX7R9BB104 |  |  |  |  | 100R
2 | 100nF. | CERAMIC-100NF-50V-10%-X7R(0805) | C0805 | C105, C106 | 302010165 |  | CC0805KRX7R9BB104 |  |  |  |  | 2.2K
1 | 2.2nF | CERAMIC-100NF-50V-10%-X7R(0805) | C0805 | C109 | 302010165 |  | CC0805KRX7R9BB104 |  |  |  |  | 220R
2 | 4.7u | CERAMIC-4.7UF-25V-10%-X5R(0805) | C0805 | C15, C101 | 302010146 |  | CC0805KKX5R8BB475 |  |  |  |  | 10K
2 | 100u | CERAMIC-100UF-6.3V-20%-X5R(1206) | C1206 | C107, C108 | 302010183 |  | GRM31CR60J107ME39L |  |  |  |  | 1K
1 | 10u | CERAMIC-100UF-6.3V-20%-X5R(1206) | C1206 | C2 | 302010183 |  | GRM31CR60J107ME39L |  |  |  |  | 4.7K
1 | Zen15 | SM6T | DO214AA | D101 | Z DIODE |  |  |  |  |  |  | 100nf
1 | SM6TDO214AA_BI | SM6TDO214AA_BI | DO214AA_BI | D104 | Z DIODE |  |  |  |  |  |  | 100nf
1 | 1N4007 | DIODE-GEN-PURPOSE-1KV-1A(DO-214AC) | DO-214AC | D112 | 304010013 |  | 1N4007 |  |  |  |  | 100nf
2 | 1N4007, | DIODE-GEN-PURPOSE-1KV-1A(DO-214AC) | DO-214AC | D102, D103 | 304010013 |  | 1N4007 |  |  |  |  | 100uf
2 | 1N4007. | DIODE-GEN-PURPOSE-1KV-1A(DO-214AC) | DO-214AC | D105, D106 | 304010013 |  | 1N4007 |  |  |  |  | 1K
2 | 1N5817 | DIODE-GEN-PURPOSE-1KV-1A(DO-214AC)DO-214AC/1206 | DO-214AC_SLIM | D107, D110 | 304010013 |  |  |  |  |  |  | 220R
2 | 1N5817. | DIODE-GEN-PURPOSE-1KV-1A(DO-214AC)DO-214AC/1206 | DO-214AC_SLIM | D108, D109 | 304010013 |  |  |  |  |  |  | 10K
2 | SS12 | DIODE-GEN-PURPOSE-1KV-1A(DO-214AC)DO-214AC/1206 | DO-214AC_SLIM | D1, D2 | 304010013 |  |  |  |  |  |  | 4.7K
1 | -1000 | SMD-RES-100R-5%-1/8W(0805) | R0805 | R142 | 301010319 |  | RC0805JR-07100RL |  |  |  |  | 1N4007
1 | -1002 | SMD-RES-10K-1%-1/8W(0805) | R0805 | R144 | 301010361 |  | RC0805FR-0710KL |  |  |  |  | 1N4007
1 | -101 | SMD-RES-100R-5%-1/8W(0805) | R0805 | R143 | 301010319 |  | RC0805JR-07100RL
3 | 100 | SMD-RES-2.2K-5%-1/8W(0805) | R0805 | R12, R13, R138 | 301010333 |  | RC0805JR-072K2L
1 | 100 | SMD-RES-220R-5%-1/8W(0805) | R0805 | R4 | 301010315 |  | RC0805JR-07220RL |  |  |  |  | 100nf
5 | 1002 | SMD-RES-10K-1%-1/8W(0805) | R0805 | R107, R108, R120, R124, R132 | 301010361 |  | RC0805FR-0710KL
2 | 1002 | SMD-RES-1K-5%-1/8W(0805) | R0805 | R113, R114 | 301010311 |  | RC0805JR-071KL
1 | 1002 | SMD-RES-4.7K-5%-1/8W(0805) | R0805 | R146 | 301010306 |  | RC0805JR-074K7L |  |  |  |  | 1K
3 | 102 | SMD-RES-1K-5%-1/8W(0805) | R0805 | R101, R112, R128 | 301010311 |  | RC0805JR-071KL |  |  |  |  | 2.2K
1 | 102 | SMD-RES-220R-5%-1/8W(0805) | R0805 | R115 | 301010315 |  | RC0805JR-07220RL |  |  |  |  | 10K
10 | 104 | SMD-RES-10K-1%-1/8W(0805) | R0805 | R1, R2, R3, R109, R110, R111, R125, R130, R135, R141 | 301010361 |  | RC0805FR-0710KL |  |  |  |  | 4.7K
1 | 104 | SMD-RES-4.7K-5%-1/8W(0805) | R0805 | R10 | 301010306 |  | RC0805JR-074K7L
2 | 1502 | SMD-RES-10K-1%-1/8W(0805) | R0805 | R121, R131 | 301010361 |  | RC0805FR-0710KL |  |  |  |  | 4.7uf
1 | 2201 | SMD-RES-1K-5%-1/8W(0805) | R0805 | R6 | 301010311 |  | RC0805JR-071KL
2 | 2201 | SMD-RES-2.2K-5%-1/8W(0805) | R0805 | R119, R133 | 301010333 |  | RC0805JR-072K2L
1 | 2702 | SMD-RES-10K-1%-1/8W(0805) | R0805 | R140 | 301010361 |  | RC0805FR-0710KL
4 | 2702 | SMD-RES-4.7K-5%-1/8W(0805) | R0805 | R117, R122, R123, R145 | 301010306 |  | RC0805JR-074K7L |  |  |  |  | 4.7K
4 | 4701 | SMD-RES-4.7K-5%-1/8W(0805) | R0805 | R8, R105, R116, R126 | 301010306 |  | RC0805JR-074K7L
5 | 13 | SMD-RES-13R-5%-1/4W(1206) | R1206 | R5, R9, R102, R106, R134 | 301010405 |  | RC1206JR-0713RL
1 | 555 | NE555D | SO08 | IC110 | TIMER
1 | LM2904 | LM358D | SO08 | IC101 | OP AMP also LM158; LM258; LM2904
1 | LM339 | LM339D | SO14 | IC108 | Low Power Low Offset Voltage Quad Comparators |  |  |  |  |  |  | BSS138W-7-F
1 | 4028 | 4028D | SO16 | IC105 | BCD to decimal DECODER
1 | 4538 | 4538D | SO16 | IC111 | Dual precision monostable MULTIVIBRATOR
1 | ULN2004 | ULN2004AD | SO16 | IC107 | DRIVER ARRAY
1 | Zen11 | CGRM4001-G | SOD-123_MINI-SMA | D4 | Molded plasitc,JEDEC SOD-123/Mini SMA
4 | J1 | SMD-MOSFET-N-CH-50V-200MA-BSS138W-7-F(SOT-23) | SOT-23 | Q1, Q3, Q106, Q107 | 305030000 |  | BSS138W-7-F
3 | BA | PNP-TRANSISTOR_SOT89 | SOT89 | Q2, Q104, Q105 | PNP TRANSISTOR
2 | BA. | PNP-TRANSISTOR_SOT89 | SOT89 | Q101, Q102 | PNP TRANSISTOR
1 | MY | NPN-TRANSISTOR_SOT89 | SOT89 | Q103 | NPN TRANSISTOR
1 | 78L06 | 78LXXSOT89_ROUND | SOT89_ROUND | IC102
1 | 78L10 | 78LXXSOT89_ROUND | SOT89_ROUND | IC104
1 | 317TO202H_NOHOLE | 317TO202H_NOHOLE | TO220H_NOHOLE | IC109 | Positive VOLTAGE REGULATOR
4 | 47 | R-EU_V235/17_1MM | V235/17_1MM | R127, R129, R136, R137 | RESISTOR, European symbol
